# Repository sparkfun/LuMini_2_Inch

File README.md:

SparkFun LuMini 2 Inch Ring
========================================

[*LuMini LED Ring - 2 Inch (COM-14966)*](https://www.sparkfun.com/products/14966)

The LuMini rings are a great way to add high density light rings to your project. They use APA102 LEDs to provide bright colors and fast data rates.

Repository Contents
-------------------

* **/Firmware** - Example code 
* **/Hardware** - Eagle design files (.brd, .sch)

Documentation
--------------
* **[Installing an Arduino Library Guide](https://learn.sparkfun.com/tutorials/installing-an-arduino-library)** - Basic information on how to install an Arduino library.
* **[Library Repository](https://github.com/FastLED/FastLED)** - Arduino library for the APA102.
* **[Hookup Guide](https://learn.sparkfun.com/tutorials/lumini-ring-hookup-guide)** - Basic hookup guide for the LuMini Rings.

Product Versions
----------------
* [COM-14966](https://www.sparkfun.com/products/14966)- 2 Inch LED Ring

License Information
-------------------

This product is _**open source**_! 

Please review the LICENSE.md file for license information. 

If you have any questions or concerns on licensing, please contact techsupport@sparkfun.com.

Distributed as-is; no warranty is given.

- Your friends at SparkFun.

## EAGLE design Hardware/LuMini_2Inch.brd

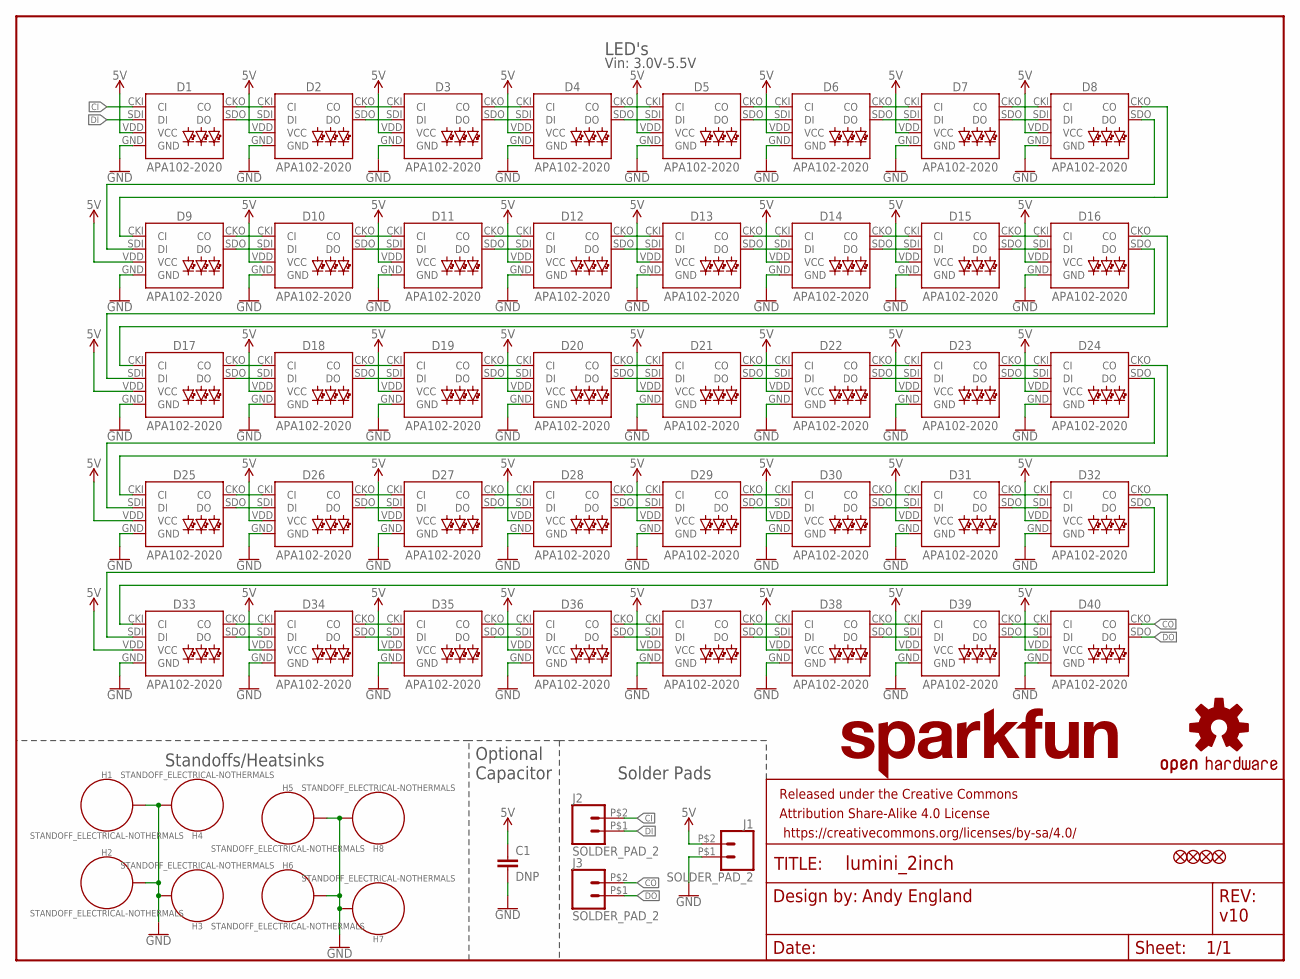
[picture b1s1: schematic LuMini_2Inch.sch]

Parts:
C1: DNP; 1206
D1, D2, D3, D4, D5, D6, D7, D8, D9, D10, D11, D12, D13, D14, D15, D16, D17, D18, D19, D20, D21, D22, D23, D24, D25, D26, D27, D28, D29, D30, D31, D32, D33, D34, D35, D36, D37, D38, D39, D40: APA102-2020
FD1, FD2, FD3, FD4: FIDUCIALUFIDUCIAL; FIDUCIAL-MICRO
FRAME1: FRAME-LETTER; CREATIVE_COMMONS
H1, H2, H3, H4, H5, H6, H7, H8: STANDOFF_ELECTRICAL-NOTHERMALS; STANDOFF-ELECTRICAL-NOTHERMALS
J1, J2, J3: SOLDER_PAD_2
LOGO1: OSHW-LOGOS; OSHW-LOGO-S
LOGO2: SFE_LOGO_NAME.1_INCH; SFE_LOGO_NAME_.1

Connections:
5V: C1.1, D1.VDD (VCC), D2.VDD (VCC), D3.VDD (VCC), D4.VDD (VCC), D5.VDD (VCC), D6.VDD (VCC), D7.VDD (VCC), D8.VDD (VCC), D9.VDD (VCC), D10.VDD (VCC), D11.VDD (VCC), D12.VDD (VCC), D13.VDD (VCC), D14.VDD (VCC), D15.VDD (VCC), D16.VDD (VCC), D17.VDD (VCC), D18.VDD (VCC), D19.VDD (VCC), D20.VDD (VCC), D21.VDD (VCC), D22.VDD (VCC), D23.VDD (VCC), D24.VDD (VCC), D25.VDD (VCC), D26.VDD (VCC), D27.VDD (VCC), D28.VDD (VCC), D29.VDD (VCC), D30.VDD (VCC), D31.VDD (VCC), D32.VDD (VCC), D33.VDD (VCC), D34.VDD (VCC), D35.VDD (VCC), D36.VDD (VCC), D37.VDD (VCC), D38.VDD (VCC), D39.VDD (VCC), D40.VDD (VCC), J1.P$2 (2)
CI: D1.CKI (CI), J2.P$2 (2)
CO: D40.CKO (CO), J3.P$2 (2)
DI: D1.SDI (DI), J2.P$1 (1)
DO: D40.SDO (DO), J3.P$1 (1)
GND: C1.2, D1.GND, D2.GND, D3.GND, D4.GND, D5.GND, D6.GND, D7.GND, D8.GND, D9.GND, D10.GND, D11.GND, D12.GND, D13.GND, D14.GND, D15.GND, D16.GND, D17.GND, D18.GND, D19.GND, D20.GND, D21.GND, D22.GND, D23.GND, D24.GND, D25.GND, D26.GND, D27.GND, D28.GND, D29.GND, D30.GND, D31.GND, D32.GND, D33.GND, D34.GND, D35.GND, D36.GND, D37.GND, D38.GND, D39.GND, D40.GND, H1.P1, H2.P1, H3.P1, H4.P1, H5.P1, H6.P1, H7.P1, H8.P1, J1.P$1 (1)
unnamed: D4.CKO (CO), D5.CKI (CI)
unnamed: D1.CKO (CO), D2.CKI (CI)
unnamed: D1.SDO (DO), D2.SDI (DI)
unnamed: D2.CKO (CO), D3.CKI (CI)
unnamed: D2.SDO (DO), D3.SDI (DI)
unnamed: D3.CKO (CO), D4.CKI (CI)
unnamed: D3.SDO (DO), D4.SDI (DI)
unnamed: D4.SDO (DO), D5.SDI (DI)
unnamed: D5.CKO (CO), D6.CKI (CI)
unnamed: D5.SDO (DO), D6.SDI (DI)
unnamed: D6.CKO (CO), D7.CKI (CI)
unnamed: D6.SDO (DO), D7.SDI (DI)
unnamed: D7.CKO (CO), D8.CKI (CI)
unnamed: D7.SDO (DO), D8.SDI (DI)
unnamed: D24.CKO (CO), D25.CKI (CI)
unnamed: D9.CKO (CO), D10.CKI (CI)
unnamed: D9.SDO (DO), D10.SDI (DI)
unnamed: D10.CKO (CO), D11.CKI (CI)
unnamed: D10.SDO (DO), D11.SDI (DI)
unnamed: D11.CKO (CO), D12.CKI (CI)
unnamed: D11.SDO (DO), D12.SDI (DI)
unnamed: D12.CKO (CO), D13.CKI (CI)
unnamed: D12.SDO (DO), D13.SDI (DI)
unnamed: D13.CKO (CO), D14.CKI (CI)
unnamed: D13.SDO (DO), D14.SDI (DI)
unnamed: D14.CKO (CO), D15.CKI (CI)
unnamed: D14.SDO (DO), D15.SDI (DI)
unnamed: D15.CKO (CO), D16.CKI (CI)
unnamed: D15.SDO (DO), D16.SDI (DI)
unnamed: D17.CKO (CO), D18.CKI (CI)
unnamed: D17.SDO (DO), D18.SDI (DI)
unnamed: D18.CKO (CO), D19.CKI (CI)
unnamed: D18.SDO (DO), D19.SDI (DI)
unnamed: D19.CKO (CO), D20.CKI (CI)
unnamed: D19.SDO (DO), D20.SDI (DI)
unnamed: D20.CKO (CO), D21.CKI (CI)
unnamed: D20.SDO (DO), D21.SDI (DI)
unnamed: D16.SDO (DO), D17.SDI (DI)
unnamed: D16.CKO (CO), D17.CKI (CI)
unnamed: D8.SDO (DO), D9.SDI (DI)
unnamed: D24.SDO (DO), D25.SDI (DI)
unnamed: D21.CKO (CO), D22.CKI (CI)
unnamed: D21.SDO (DO), D22.SDI (DI)
unnamed: D22.CKO (CO), D23.CKI (CI)
unnamed: D22.SDO (DO), D23.SDI (DI)
unnamed: D23.CKO (CO), D24.CKI (CI)
unnamed: D23.SDO (DO), D24.SDI (DI)
unnamed: D32.SDO (DO), D33.SDI (DI)
unnamed: D32.CKO (CO), D33.CKI (CI)
unnamed: D25.CKO (CO), D26.CKI (CI)
unnamed: D25.SDO (DO), D26.SDI (DI)
unnamed: D26.CKO (CO), D27.CKI (CI)
unnamed: D26.SDO (DO), D27.SDI (DI)
unnamed: D27.CKO (CO), D28.CKI (CI)
unnamed: D27.SDO (DO), D28.SDI (DI)
unnamed: D28.CKO (CO), D29.CKI (CI)
unnamed: D28.SDO (DO), D29.SDI (DI)
unnamed: D29.CKO (CO), D30.CKI (CI)
unnamed: D29.SDO (DO), D30.SDI (DI)
unnamed: D30.CKO (CO), D31.CKI (CI)
unnamed: D30.SDO (DO), D31.SDI (DI)
unnamed: D31.CKO (CO), D32.CKI (CI)
unnamed: D31.SDO (DO), D32.SDI (DI)
unnamed: D33.CKO (CO), D34.CKI (CI)
unnamed: D33.SDO (DO), D34.SDI (DI)
unnamed: D34.CKO (CO), D35.CKI (CI)
unnamed: D34.SDO (DO), D35.SDI (DI)
unnamed: D35.CKO (CO), D36.CKI (CI)
unnamed: D35.SDO (DO), D36.SDI (DI)
unnamed: D36.CKO (CO), D37.CKI (CI)
unnamed: D36.SDO (DO), D37.SDI (DI)
unnamed: D37.CKO (CO), D38.CKI (CI)
unnamed: D37.SDO (DO), D38.SDI (DI)
unnamed: D38.CKO (CO), D39.CKI (CI)
unnamed: D38.SDO (DO), D39.SDI (DI)
unnamed: D39.CKO (CO), D40.CKI (CI)
unnamed: D39.SDO (DO), D40.SDI (DI)
unnamed: D8.CKO (CO), D9.CKI (CI)

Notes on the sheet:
v10
Andy England
Optional Capacitor
Standoffs/Heatsinks
LED's
Vin: 3.0V-5.5V
Solder Pads

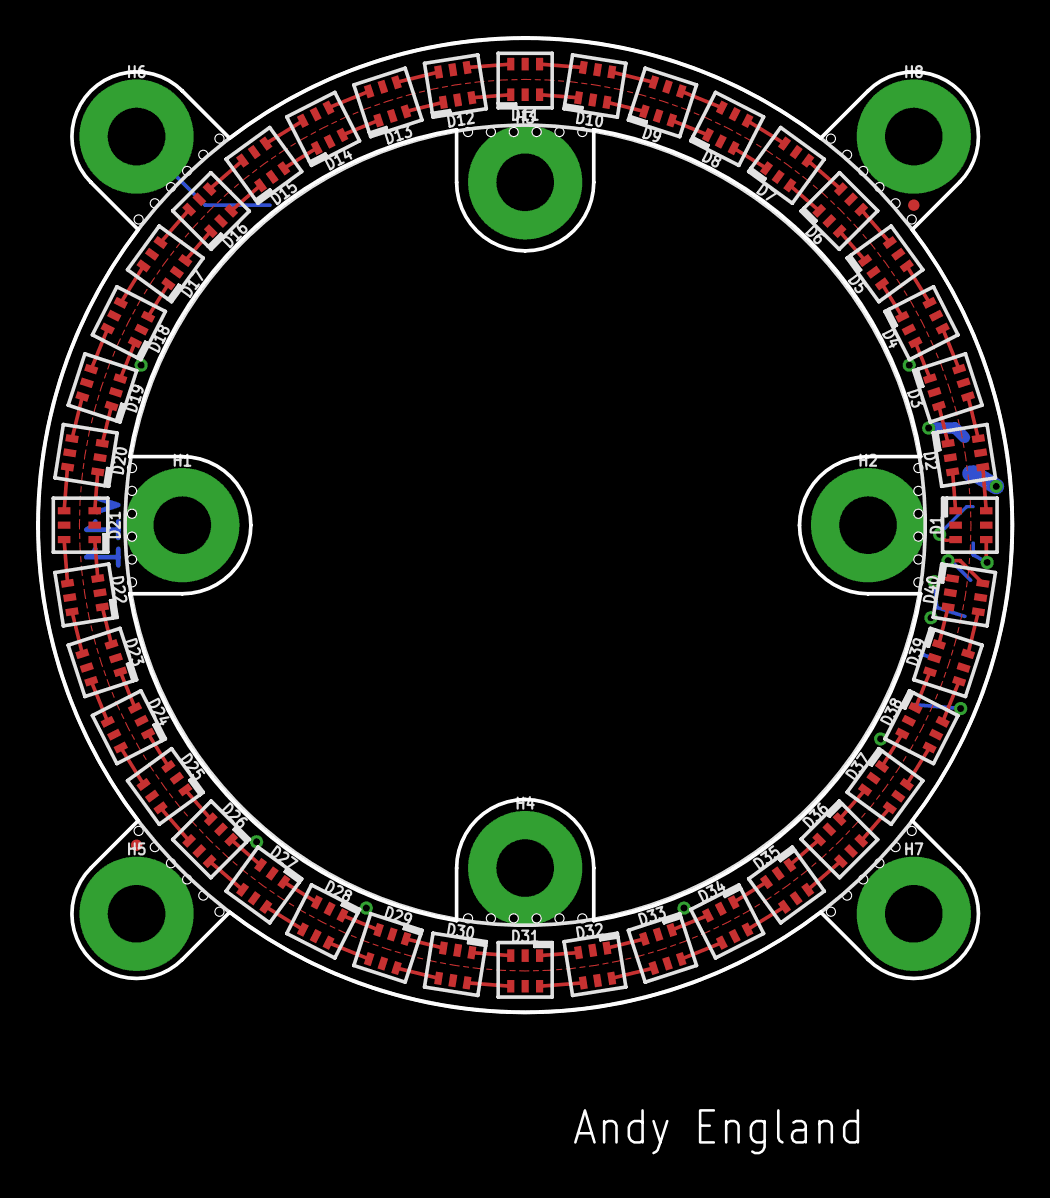
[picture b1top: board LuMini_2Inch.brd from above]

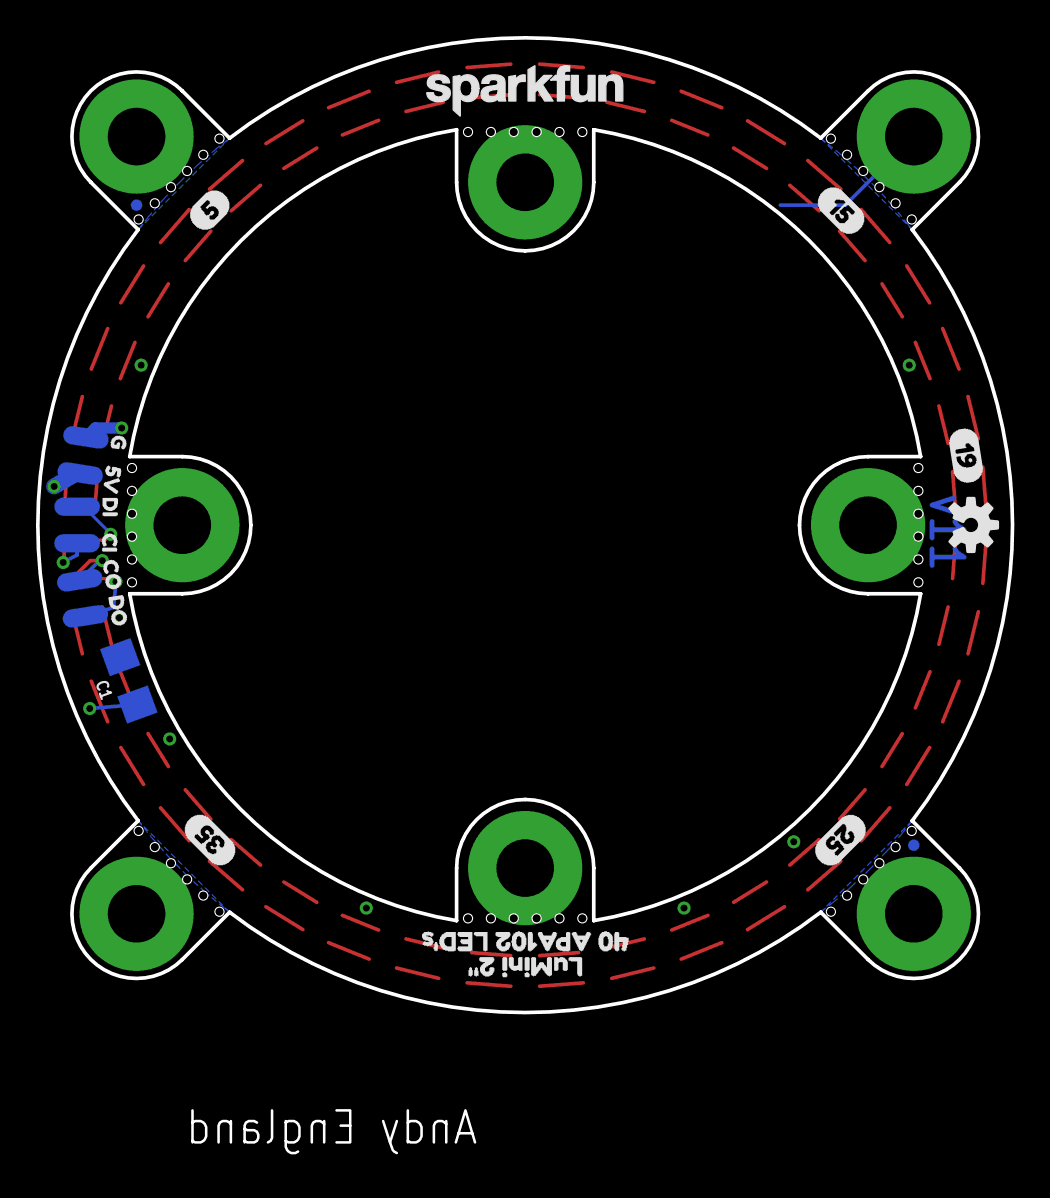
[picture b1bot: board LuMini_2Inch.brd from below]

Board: 2 copper layers, 54.2 x 54.2 mm, 73 parts (21 on the bottom side), 84 nets.

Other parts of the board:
U$1: LUMINI_2#0
U$2: 54
U$3: 156
U$4: 5V6
U$5: G4
U$6: 194
U$7: DO3
U$8: CO1
U$9: CI6
U$10: DI4
U$11: 40_APA102_LED#S1
U$12: 258
U$13: 3510
U$14: ORDERING_INSTRUCTIONS

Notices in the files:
parts and their libraries:
SparkFun-LED: Licensing: Creative Commons ShareAlike 4.0 International - https://creativecommons.org/licenses/by-sa/4.0
SparkFun-Aesthetics: Released under the Creative Commons Attribution Share-Alike 4.0 License
SparkFun-Aesthetics: https://creativecommons.org/licenses/by-sa/4.0
